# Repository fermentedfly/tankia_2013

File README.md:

# TANKIA 2013
There Are [still] No Kangaroos In Austria

This repository contains hard & software for TANKIA 2013 developed after end of season 2013

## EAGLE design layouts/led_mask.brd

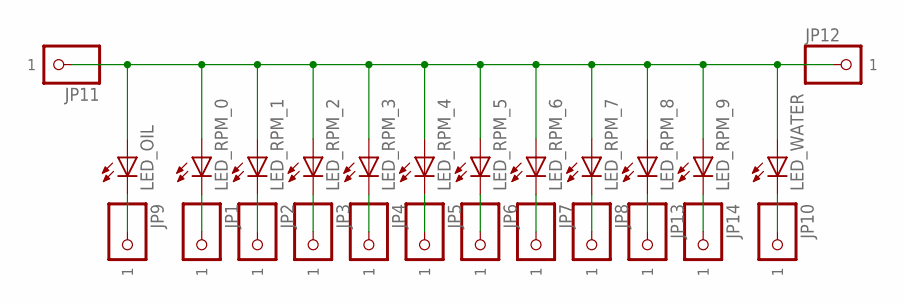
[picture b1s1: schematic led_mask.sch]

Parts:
JP1, JP2, JP3, JP4, JP5, JP6, JP7, JP8, JP9, JP10, JP11, JP12, JP13, JP14: PINHD-1X11.5X2.5MM_SMD; 1XSMD1.5X2.5MM
LED_OIL: LED3MM
LED_RPM_0, LED_RPM_1, LED_RPM_2, LED_RPM_3, LED_RPM_4, LED_RPM_5, LED_RPM_6, LED_RPM_7, LED_RPM_8, LED_RPM_9: LED3MM
LED_WATER: LED3MM

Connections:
unnamed: JP11.P$1, JP12.P$1, LED_OIL.A, LED_RPM_0.A, LED_RPM_1.A, LED_RPM_2.A, LED_RPM_3.A, LED_RPM_4.A, LED_RPM_5.A, LED_RPM_6.A, LED_RPM_7.A, LED_RPM_8.A, LED_RPM_9.A, LED_WATER.A
unnamed: JP3.P$1, LED_RPM_2.K (C)
unnamed: JP1.P$1, LED_RPM_0.K (C)
unnamed: JP2.P$1, LED_RPM_1.K (C)
unnamed: JP4.P$1, LED_RPM_3.K (C)
unnamed: JP5.P$1, LED_RPM_4.K (C)
unnamed: JP6.P$1, LED_RPM_5.K (C)
unnamed: JP7.P$1, LED_RPM_6.K (C)
unnamed: JP8.P$1, LED_RPM_7.K (C)
unnamed: JP9.P$1, LED_OIL.K (C)
unnamed: JP10.P$1, LED_WATER.K (C)
unnamed: JP13.P$1, LED_RPM_8.K (C)
unnamed: JP14.P$1, LED_RPM_9.K (C)

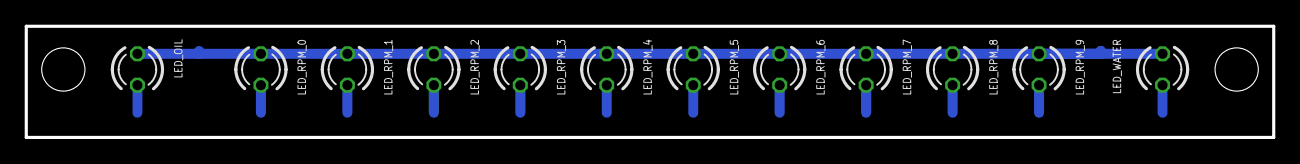
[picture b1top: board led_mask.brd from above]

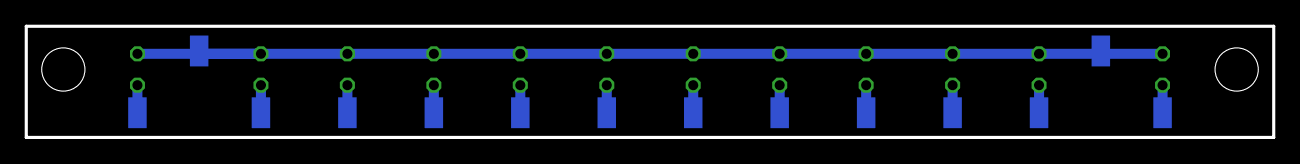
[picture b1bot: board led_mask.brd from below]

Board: 2 copper layers, 101.0 x 9.0 mm, 26 parts (14 on the bottom side), 13 nets.

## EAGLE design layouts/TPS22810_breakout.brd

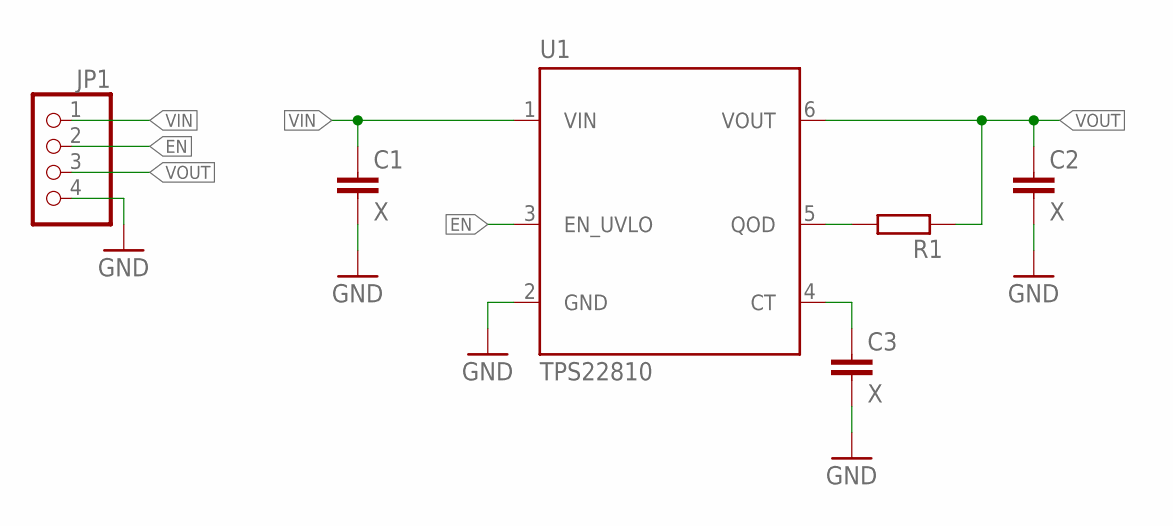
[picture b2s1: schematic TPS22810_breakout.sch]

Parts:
C1, C2, C3: X; C0603
JP1: PINHD-1X4; 1X04
R1: R-EU_R0603; R0603
U1: TPS22810; DBV-R-PDSO-G6

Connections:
EN: JP1.2, U1.3 (EN_UVLO)
GND: C1.2, C2.2, C3.2, JP1.4, U1.2 (GND)
unnamed: R1.2, U1.5 (QOD)
unnamed: C3.1, U1.4 (CT)
VIN: C1.1, JP1.1, U1.1 (VIN)
VOUT: C2.1, JP1.3, R1.1, U1.6 (VOUT)

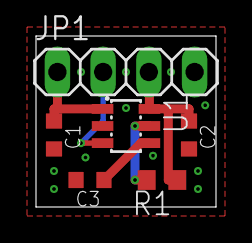
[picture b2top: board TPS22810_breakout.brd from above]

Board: 2 copper layers, 10.0 x 9.5 mm, 6 parts (0 on the bottom side), 6 nets.

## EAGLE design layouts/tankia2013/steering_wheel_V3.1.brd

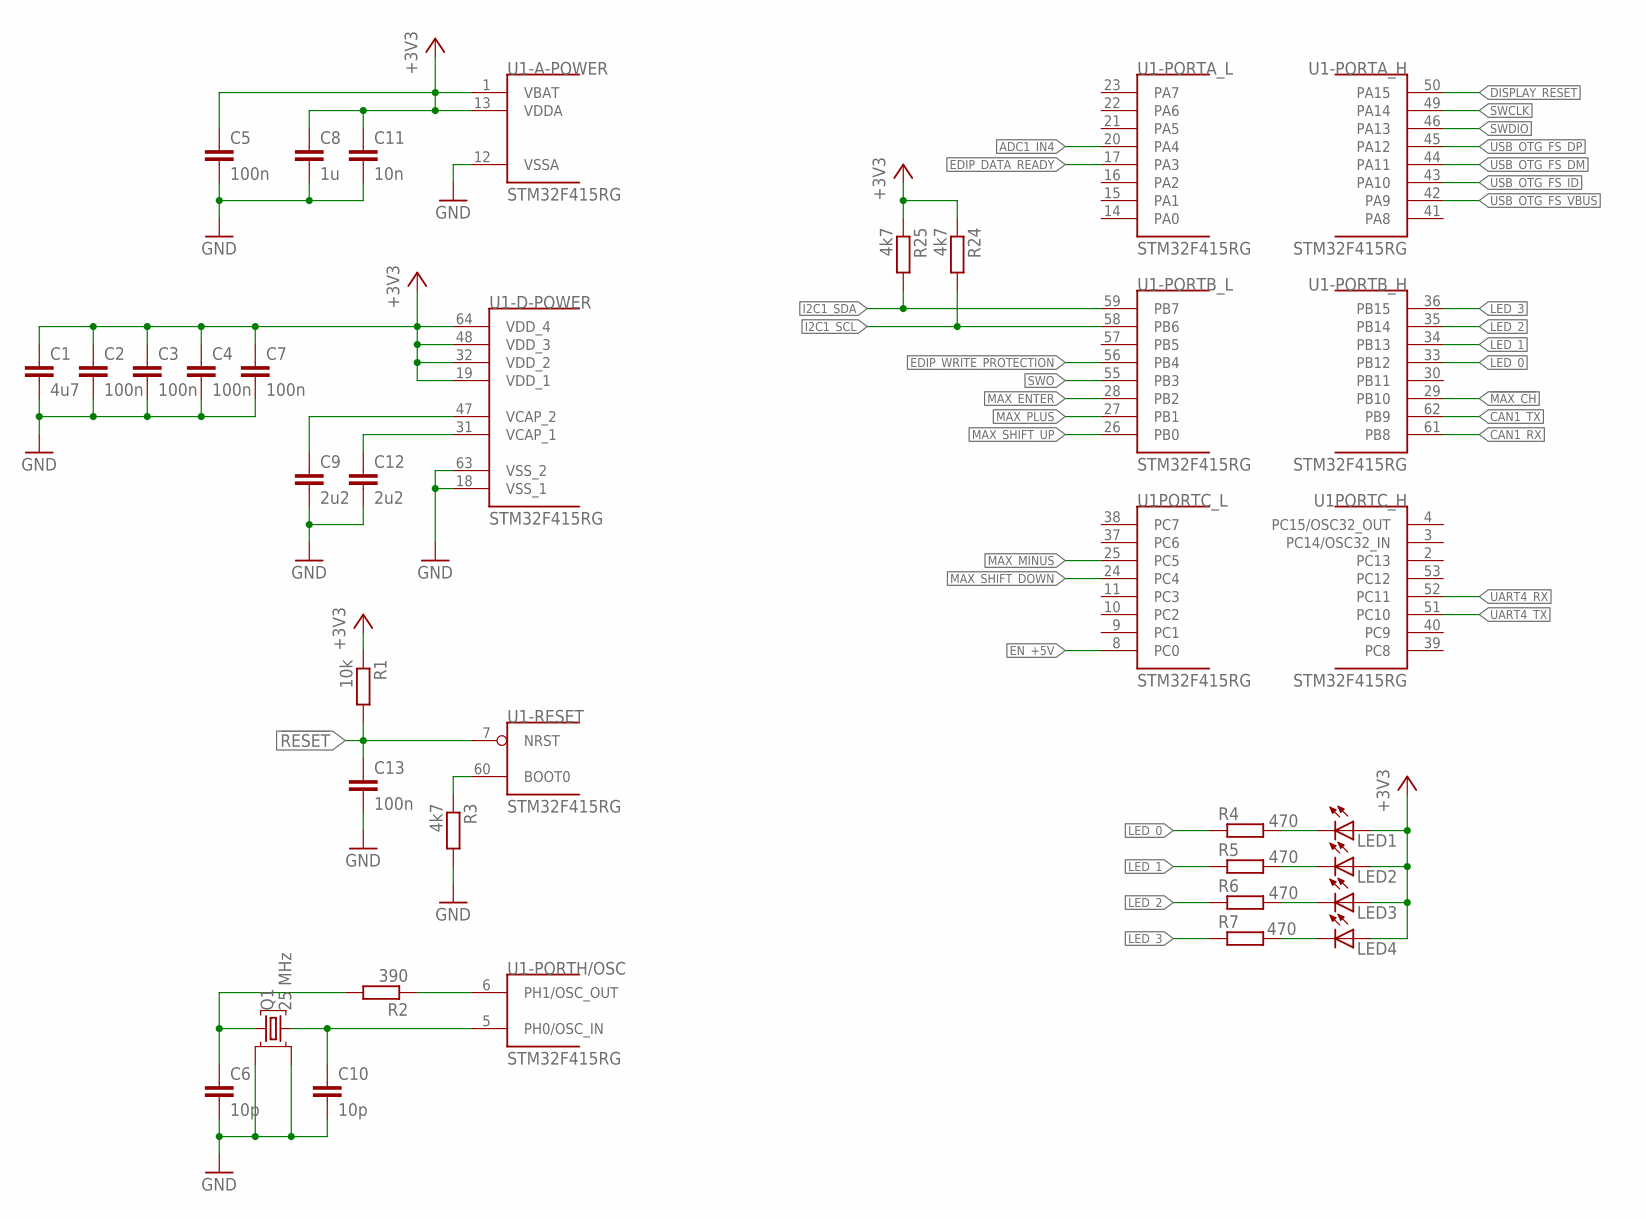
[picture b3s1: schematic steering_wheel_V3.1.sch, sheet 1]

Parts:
C1: 4u7; C0603
C2, C3, C4, C5, C7, C13: 100n; C0603
C6, C10: 10p; C0603
C8: 1u; C0603
C9, C12: 2u2; C0603
C11: 10n; C0603
LED1, LED2, LED3, LED4: LEDCHIPLED_0603; CHIPLED_0603
Q1: 25 MHz; 3.2X2.5MM-SMD
R1: 10k; R0603
R2: 390; R0603
R3, R24, R25: 4k7; R0603
R4, R5, R6, R7: 470; R0603
U1: STM32F415RG; LQFP64

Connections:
!MAX_CH: U1.29 (PB10); also elsewhere on the board
!RESET: C13.1, R1.2, U1.7 (NRST); also elsewhere on the board
+3V3: C1.1, C2.1, C3.1, C4.1, C5.1, C7.1, C8.1, C11.1, LED1.A, LED2.A, LED3.A, LED4.A, R1.1, R24.1, R25.1, U1.1 (VBAT), U1.13 (VDDA), U1.19 (VDD_1), U1.32 (VDD_2), U1.48 (VDD_3), U1.64 (VDD_4); also elsewhere on the board
ADC1_IN4: U1.20 (PA4); also elsewhere on the board
CAN1_RX: U1.61 (PB8); also elsewhere on the board
CAN1_TX: U1.62 (PB9); also elsewhere on the board
DISPLAY_RESET: U1.50 (PA15); also elsewhere on the board
EDIP_DATA_READY: U1.17 (PA3); also elsewhere on the board
EDIP_WRITE_PROTECTION: U1.56 (PB4); also elsewhere on the board
EN_+5V: U1.8 (PC0); also elsewhere on the board
GND: C1.2, C2.2, C3.2, C4.2, C5.2, C6.2, C7.2, C8.2, C9.2, C10.2, C11.2, C12.2, C13.2, Q1.2 (GND1), Q1.4 (GND2), R3.2, U1.12 (VSSA), U1.18 (VSS_1), U1.63 (VSS_2); also elsewhere on the board
I2C1_SCL: R24.2, U1.58 (PB6); also elsewhere on the board
I2C1_SDA: R25.2, U1.59 (PB7); also elsewhere on the board
LED_0: R4.1, U1.33 (PB12)
LED_1: R5.1, U1.34 (PB13)
LED_2: R6.1, U1.35 (PB14)
LED_3: R7.1, U1.36 (PB15)
MAX_ENTER: U1.28 (PB2); also elsewhere on the board
MAX_MINUS: U1.25 (PC5); also elsewhere on the board
MAX_PLUS: U1.27 (PB1); also elsewhere on the board
MAX_SHIFT_DOWN: U1.24 (PC4); also elsewhere on the board
MAX_SHIFT_UP: U1.26 (PB0); also elsewhere on the board
unnamed: C9.1, U1.47 (VCAP_2)
unnamed: C12.1, U1.31 (VCAP_1)
unnamed: R2.1, U1.6 (PH1/OSC_OUT)
unnamed: C10.1, Q1.3 (Q2), U1.5 (PH0/OSC_IN)
unnamed: LED4.C, R7.2
unnamed: R3.1, U1.60 (BOOT0)
unnamed: LED2.C, R5.2
unnamed: LED3.C, R6.2
unnamed: C6.1, Q1.1 (Q1), R2.2
unnamed: LED1.C, R4.2
SWCLK: U1.49 (PA14); also elsewhere on the board
SWDIO: U1.46 (PA13); also elsewhere on the board
SWO: U1.55 (PB3); also elsewhere on the board
UART4_RX: U1.52 (PC11); also elsewhere on the board
UART4_TX: U1.51 (PC10); also elsewhere on the board
USB_OTG_FS_DM: U1.44 (PA11); also elsewhere on the board
USB_OTG_FS_DP: U1.45 (PA12); also elsewhere on the board
USB_OTG_FS_ID: U1.43 (PA10); also elsewhere on the board
USB_OTG_FS_VBUS: U1.42 (PA9); also elsewhere on the board

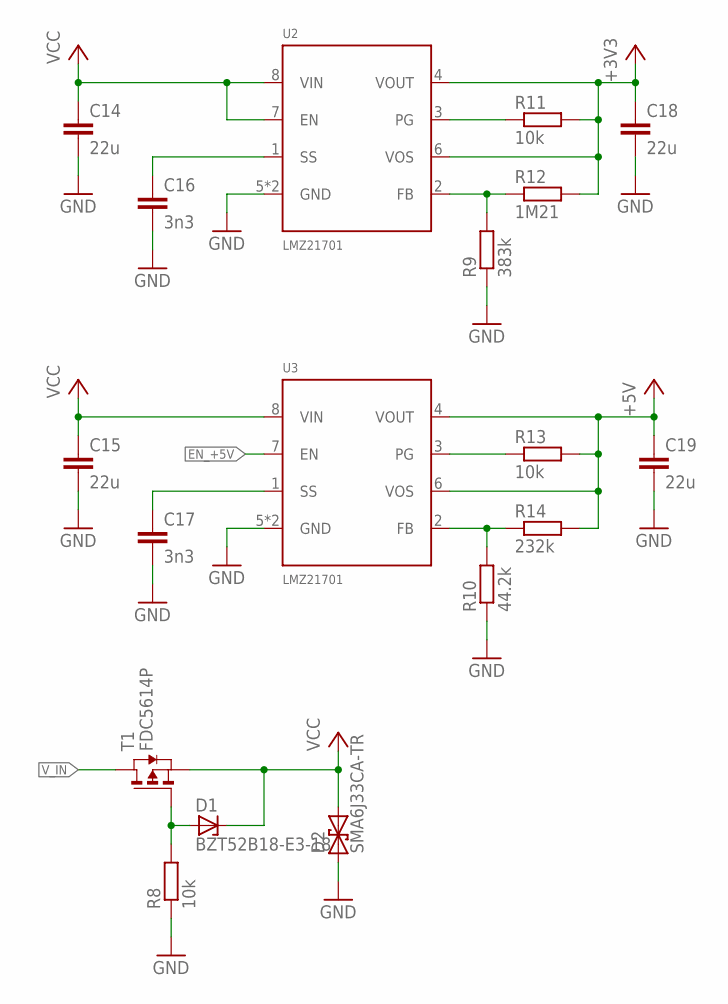
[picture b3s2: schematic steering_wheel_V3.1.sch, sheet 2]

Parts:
C14, C15, C18, C19: 22u; C1210
C16, C17: 3n3; C0603
D1: BZT52B18-E3-18; SOD123F
D2: SMA6J33CA-TR; DO214AC
R8, R11, R13: 10k; R0603
R9: 383k; R0603
R10: 44.2k; R0603
R12: 1M21; R0603
R14: 232k; R0603
T1: FDC5614P; SSOT6
U2, U3: LMZ21701; SIL0008E

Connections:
+3V3: C18.1, R11.2, R12.2, U2.4 (VOUT), U2.6 (VOS); also elsewhere on the board
+5V: C19.1, R13.2, R14.2, U3.4 (VOUT), U3.6 (VOS); also elsewhere on the board
EN_+5V: U3.7 (EN); also elsewhere on the board
GND: C14.2, C15.2, C16.2, C17.2, C18.2, C19.2, D2.A (1), R8.1, R9.1, R10.1, U2.5 (GND), U2.PAD (GND), U3.5 (GND), U3.PAD (GND); also elsewhere on the board
unnamed: D1.A, R8.2, T1.3 (G)
unnamed: C16.1, U2.1 (SS)
unnamed: C17.1, U3.1 (SS)
unnamed: R13.1, U3.3 (PG)
unnamed: R11.1, U2.3 (PG)
unnamed: R9.2, R12.1, U2.2 (FB)
unnamed: R10.2, R14.1, U3.2 (FB)
VCC: C14.1, C15.1, D1.C, D2.C (2), T1.4 (S), U2.7 (EN), U2.8 (VIN), U3.8 (VIN)
V_IN: T1.1 (D), T1.2 (D), T1.5 (D), T1.6 (D); also elsewhere on the board

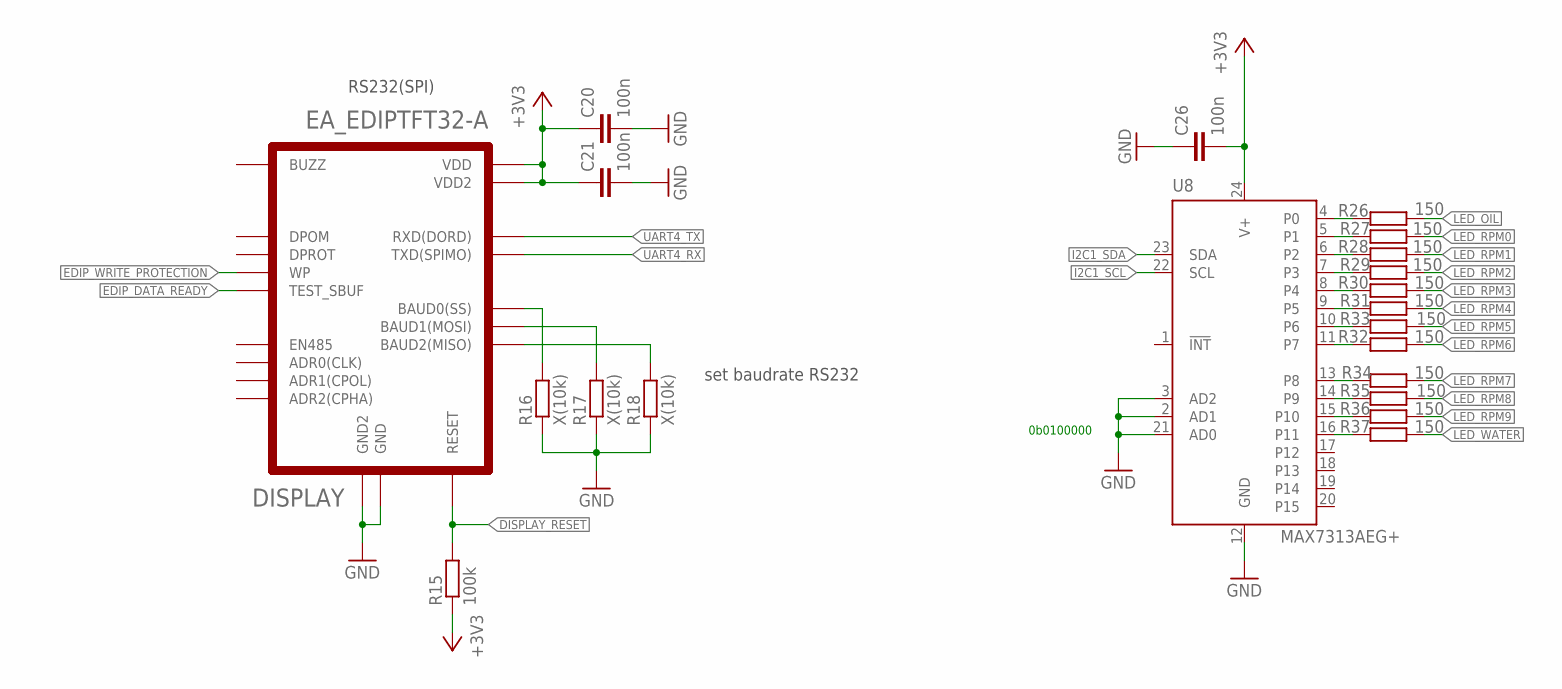
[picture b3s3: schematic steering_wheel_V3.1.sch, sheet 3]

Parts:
C20, C21, C26: 100n; C0603
DISPLAY: EA_EDIPTFT32-A; EDIPTFT32-A
R15: 100k; R0603
R16, R17, R18: X(10k); R0603
R26, R27, R28, R29, R30, R31, R32, R33, R34, R35, R36, R37: 150; R0603
U8: MAX7313AEG+; QSOP-24

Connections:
+3V3: C20.1, C21.1, C26.2, DISPLAY.P$2 (VDD), DISPLAY.P$22 (VDD2), R15.1, U8.24 (V+); also elsewhere on the board
DISPLAY_RESET: DISPLAY.P$5 (RESET), R15.2; also elsewhere on the board
EDIP_DATA_READY: DISPLAY.P$20 (TEST_SBUF); also elsewhere on the board
EDIP_WRITE_PROTECTION: DISPLAY.P$19 (WP); also elsewhere on the board
GND: C20.2, C21.2, C26.1, DISPLAY.P$1 (GND), DISPLAY.P$21 (GND2), R16.1, R17.1, R18.1, U8.2 (AD1), U8.3 (AD2), U8.12 (GND), U8.21 (AD0); also elsewhere on the board
I2C1_SCL: U8.22 (SCL); also elsewhere on the board
I2C1_SDA: U8.23 (SDA); also elsewhere on the board
LED_OIL: R26.1; also elsewhere on the board
LED_RPM0: R27.1; also elsewhere on the board
LED_RPM1: R28.1; also elsewhere on the board
LED_RPM2: R29.1; also elsewhere on the board
LED_RPM3: R30.1; also elsewhere on the board
LED_RPM4: R31.1; also elsewhere on the board
LED_RPM5: R33.1; also elsewhere on the board
LED_RPM6: R32.1; also elsewhere on the board
LED_RPM7: R34.1; also elsewhere on the board
LED_RPM8: R35.1; also elsewhere on the board
LED_RPM9: R36.1; also elsewhere on the board
LED_WATER: R37.1; also elsewhere on the board
unnamed: R26.2, U8.4 (P0)
unnamed: DISPLAY.P$8 (BAUD2(MISO)), R18.2
unnamed: R27.2, U8.5 (P1)
unnamed: DISPLAY.P$7 (BAUD1(MOSI)), R17.2
unnamed: DISPLAY.P$6 (BAUD0(SS)), R16.2
unnamed: R28.2, U8.6 (P2)
unnamed: R29.2, U8.7 (P3)
unnamed: R30.2, U8.8 (P4)
unnamed: R31.2, U8.9 (P5)
unnamed: R32.2, U8.11 (P7)
unnamed: R33.2, U8.10 (P6)
unnamed: R34.2, U8.13 (P8)
unnamed: R35.2, U8.14 (P9)
unnamed: R36.2, U8.15 (P10)
unnamed: R37.2, U8.16 (P11)
UART4_RX: DISPLAY.P$11 (TXD(SPIMO)); also elsewhere on the board
UART4_TX: DISPLAY.P$10 (RXD(DORD)); also elsewhere on the board

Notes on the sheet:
set baudrate RS232
0b0100000

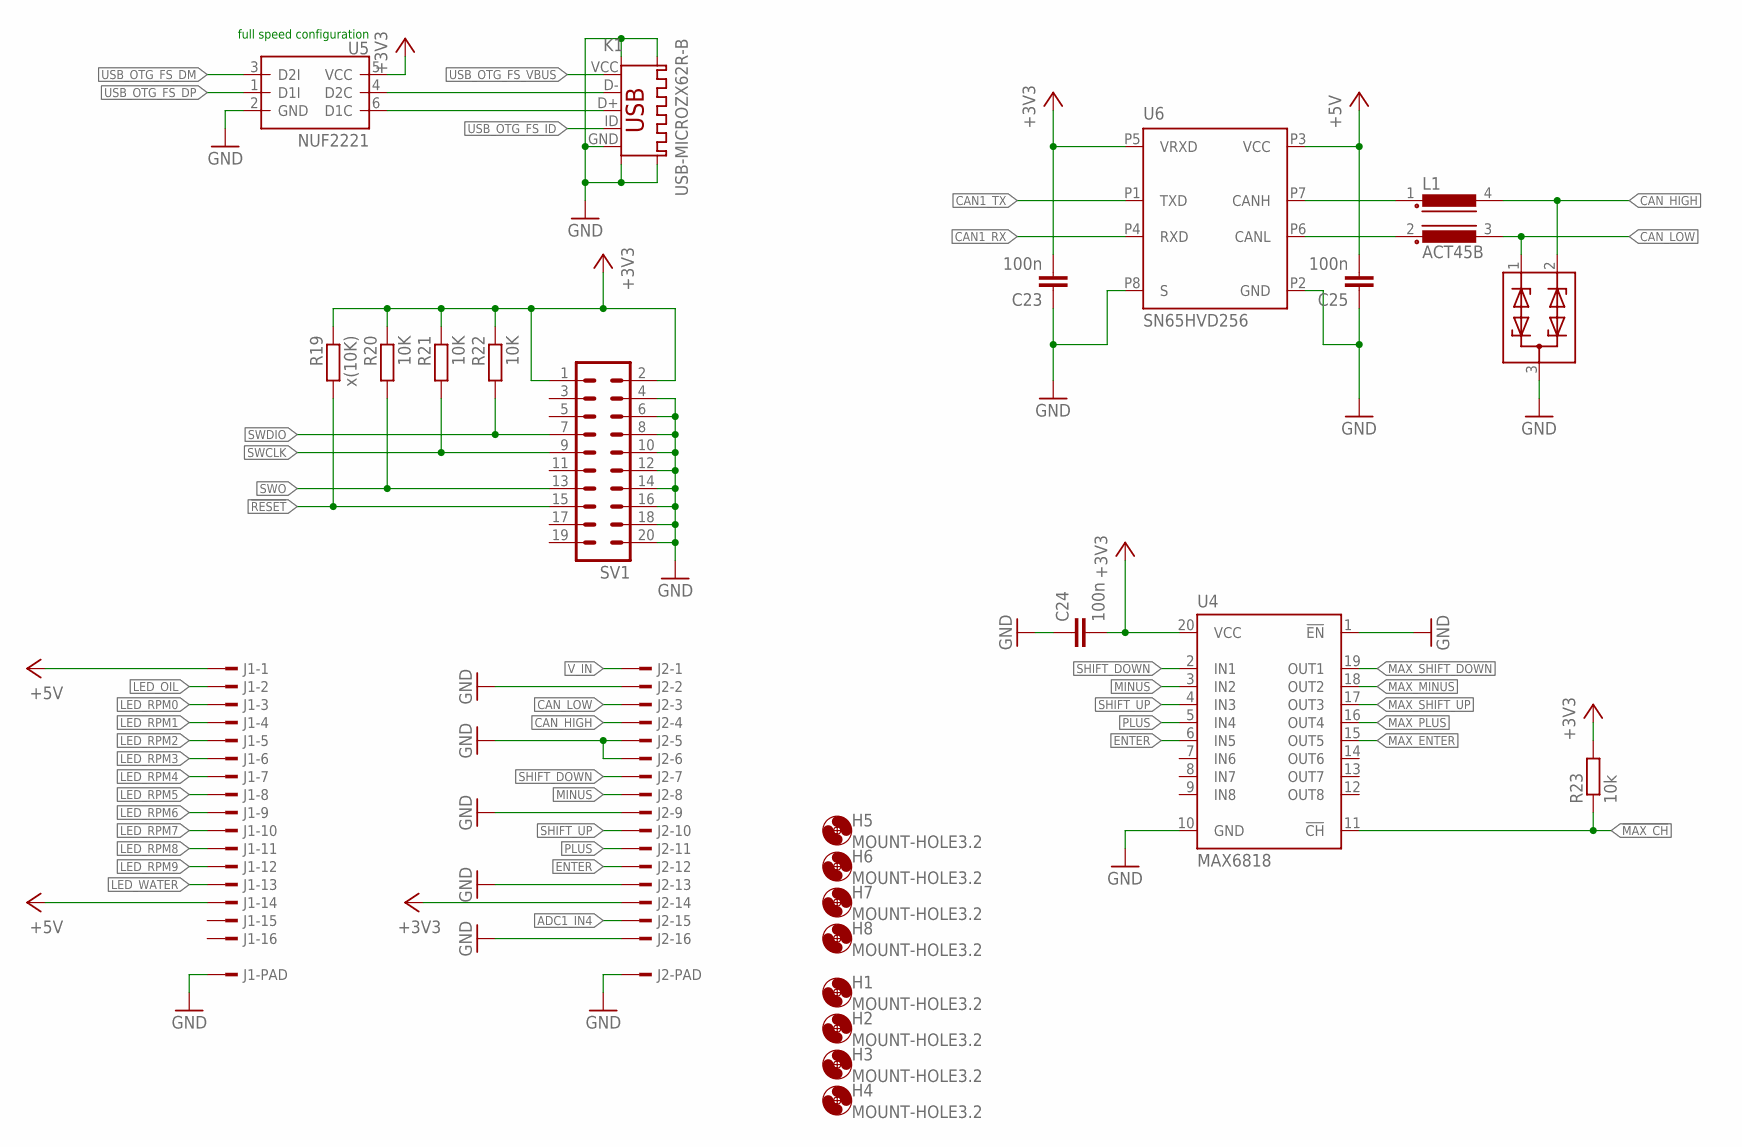
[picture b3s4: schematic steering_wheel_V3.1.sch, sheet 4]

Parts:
C23, C24, C25: 100n; C0603
D3: PESD1CAN-U; SOT-323
H1, H2, H3, H4, H5, H6, H7, H8: MOUNT-HOLE3.2; 3,2
J1, J2: 1-292227-6
K1: USB-MICROZX62R-B; ZX62R-B
L1: ACT45B
R19: x(10K); R0603
R20, R21, R22: 10K; R0603
R23: 10k; R0603
SV1: ML20
U4: MAX6818; SSOP-20
U5: NUF2221; SOT363
U6: SN65HVD256; SOIC8

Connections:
!MAX_CH: R23.1, U4.11 (!CH); also elsewhere on the board
+3V3: C23.2, C24.2, J2.14, R19.1, R20.1, R21.1, R22.1, R23.2, SV1.1, SV1.2, U4.20 (VCC), U5.5 (VCC), U6.P5 (VRXD); also elsewhere on the board
+5V: C25.2, J1.1, J1.14, U6.P3 (VCC); also elsewhere on the board
ADC1_IN4: J2.15; also elsewhere on the board
CAN1_RX: U6.P4 (RXD); also elsewhere on the board
CAN1_TX: U6.P1 (TXD); also elsewhere on the board
CAN_HIGH: D3.2, J2.4, L1.4
CAN_LOW: D3.1, J2.3, L1.3
ENTER: J2.12, U4.6 (IN5)
GND: C23.1, C24.1, C25.1, D3.3, J1.PAD1, J1.PAD2, J2.2, J2.5, J2.6, J2.9, J2.13, J2.16, J2.PAD1, J2.PAD2, K1.GND, K1.P$6 (GND3), K1.P$7 (GND4), K1.P$8 (GND1), K1.P$9 (GND2), SV1.4, SV1.6, SV1.8, SV1.10, SV1.12, SV1.14, SV1.16, SV1.18, SV1.20, U4.1 (!EN), U4.10 (GND), U5.2 (GND), U6.P2 (GND), U6.P8 (S); also elsewhere on the board
LED_OIL: J1.2; also elsewhere on the board
LED_RPM0: J1.3; also elsewhere on the board
LED_RPM1: J1.4; also elsewhere on the board
LED_RPM2: J1.5; also elsewhere on the board
LED_RPM3: J1.6; also elsewhere on the board
LED_RPM4: J1.7; also elsewhere on the board
LED_RPM5: J1.8; also elsewhere on the board
LED_RPM6: J1.9; also elsewhere on the board
LED_RPM7: J1.10; also elsewhere on the board
LED_RPM8: J1.11; also elsewhere on the board
LED_RPM9: J1.12; also elsewhere on the board
LED_WATER: J1.13; also elsewhere on the board
MAX_ENTER: U4.15 (OUT5); also elsewhere on the board
MAX_MINUS: U4.18 (OUT2); also elsewhere on the board
MAX_PLUS: U4.16 (OUT4); also elsewhere on the board
MAX_SHIFT_DOWN: U4.19 (OUT1); also elsewhere on the board
MAX_SHIFT_UP: U4.17 (OUT3); also elsewhere on the board
MINUS: J2.8, U4.3 (IN2)
unnamed: L1.1, U6.P7 (CANH)
unnamed: L1.2, U6.P6 (CANL)
unnamed: R19.2, SV1.15
PLUS: J2.11, U4.5 (IN4)
SHIFT_DOWN: J2.7, U4.2 (IN1)
SHIFT_UP: J2.10, U4.4 (IN3)
SWCLK: R21.2, SV1.9; also elsewhere on the board
SWDIO: R22.2, SV1.7; also elsewhere on the board
SWO: R20.2, SV1.13; also elsewhere on the board
USB_DM: K1.D-, U5.4 (D2C)
USB_DP: K1.D+, U5.6 (D1C)
USB_OTG_FS_DM: U5.3 (D2I); also elsewhere on the board
USB_OTG_FS_DP: U5.1 (D1I); also elsewhere on the board
USB_OTG_FS_ID: K1.ID; also elsewhere on the board
USB_OTG_FS_VBUS: K1.VCC; also elsewhere on the board
V_IN: J2.1; also elsewhere on the board

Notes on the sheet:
full speed configuration

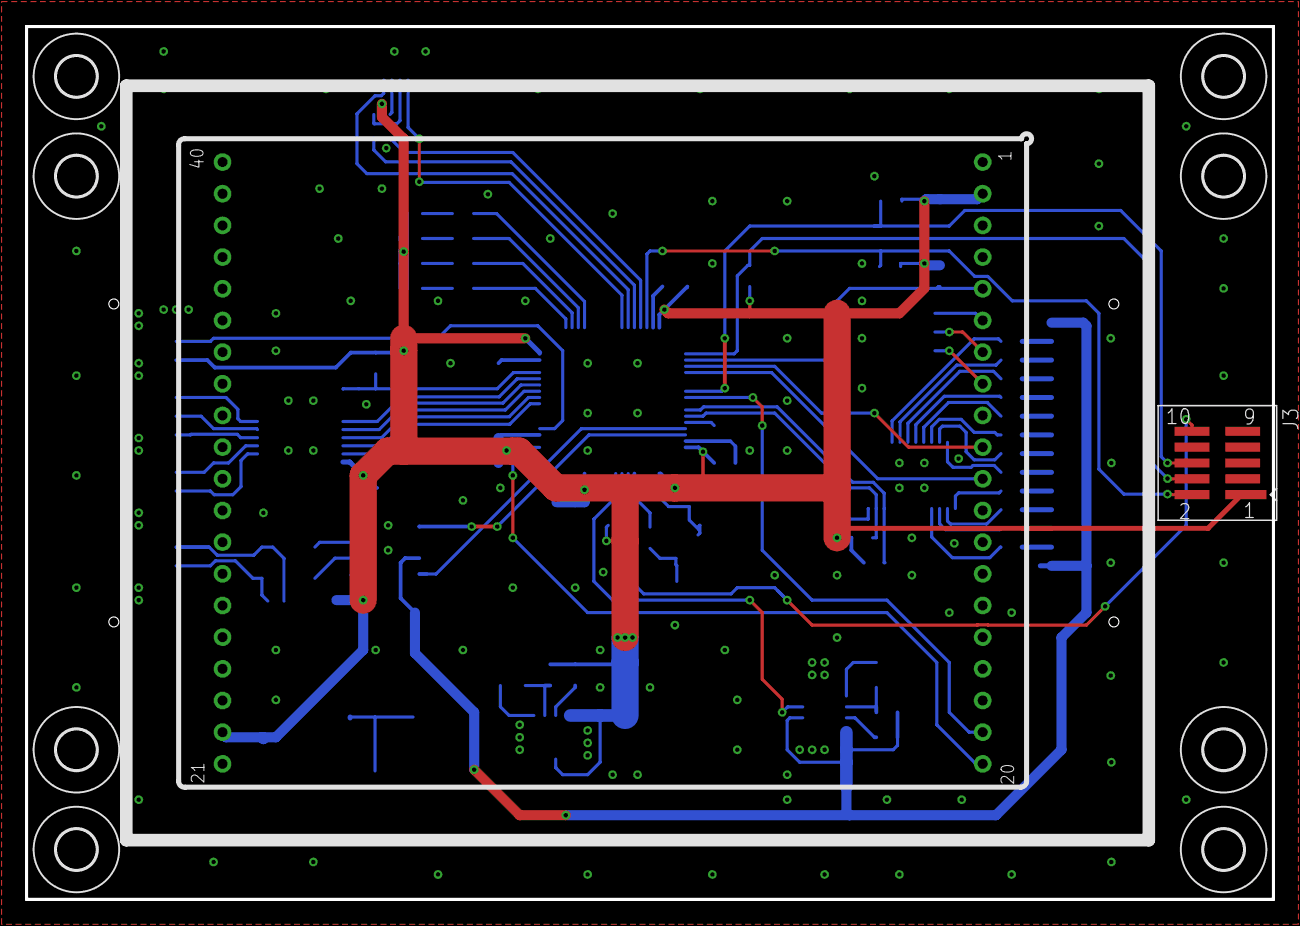
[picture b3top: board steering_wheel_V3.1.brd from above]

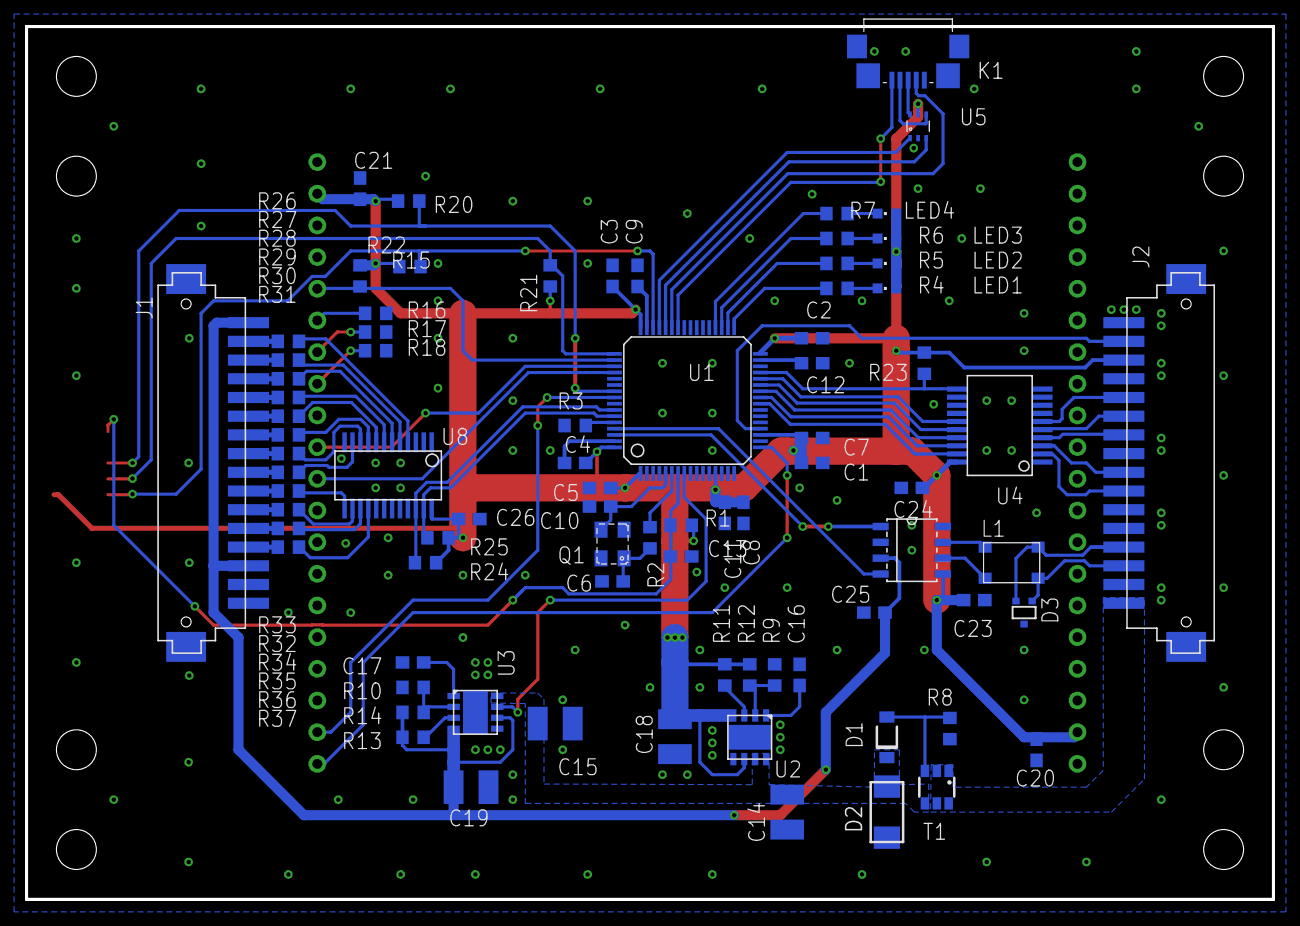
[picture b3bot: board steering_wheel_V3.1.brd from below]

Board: 2 copper layers, 100.0 x 70.0 mm, 91 parts (81 on the bottom side), 89 nets.

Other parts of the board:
J3: FTSH-105-01-F-DV-K; FTSH-105-01-XXX-DV-K

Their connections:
!RESET: J3.10; also elsewhere on the board
+3V3: J3.1; also elsewhere on the board
GND: J3.3, J3.5; also elsewhere on the board
SWCLK: J3.4; also elsewhere on the board
SWDIO: J3.2; also elsewhere on the board
SWO: J3.6; also elsewhere on the board

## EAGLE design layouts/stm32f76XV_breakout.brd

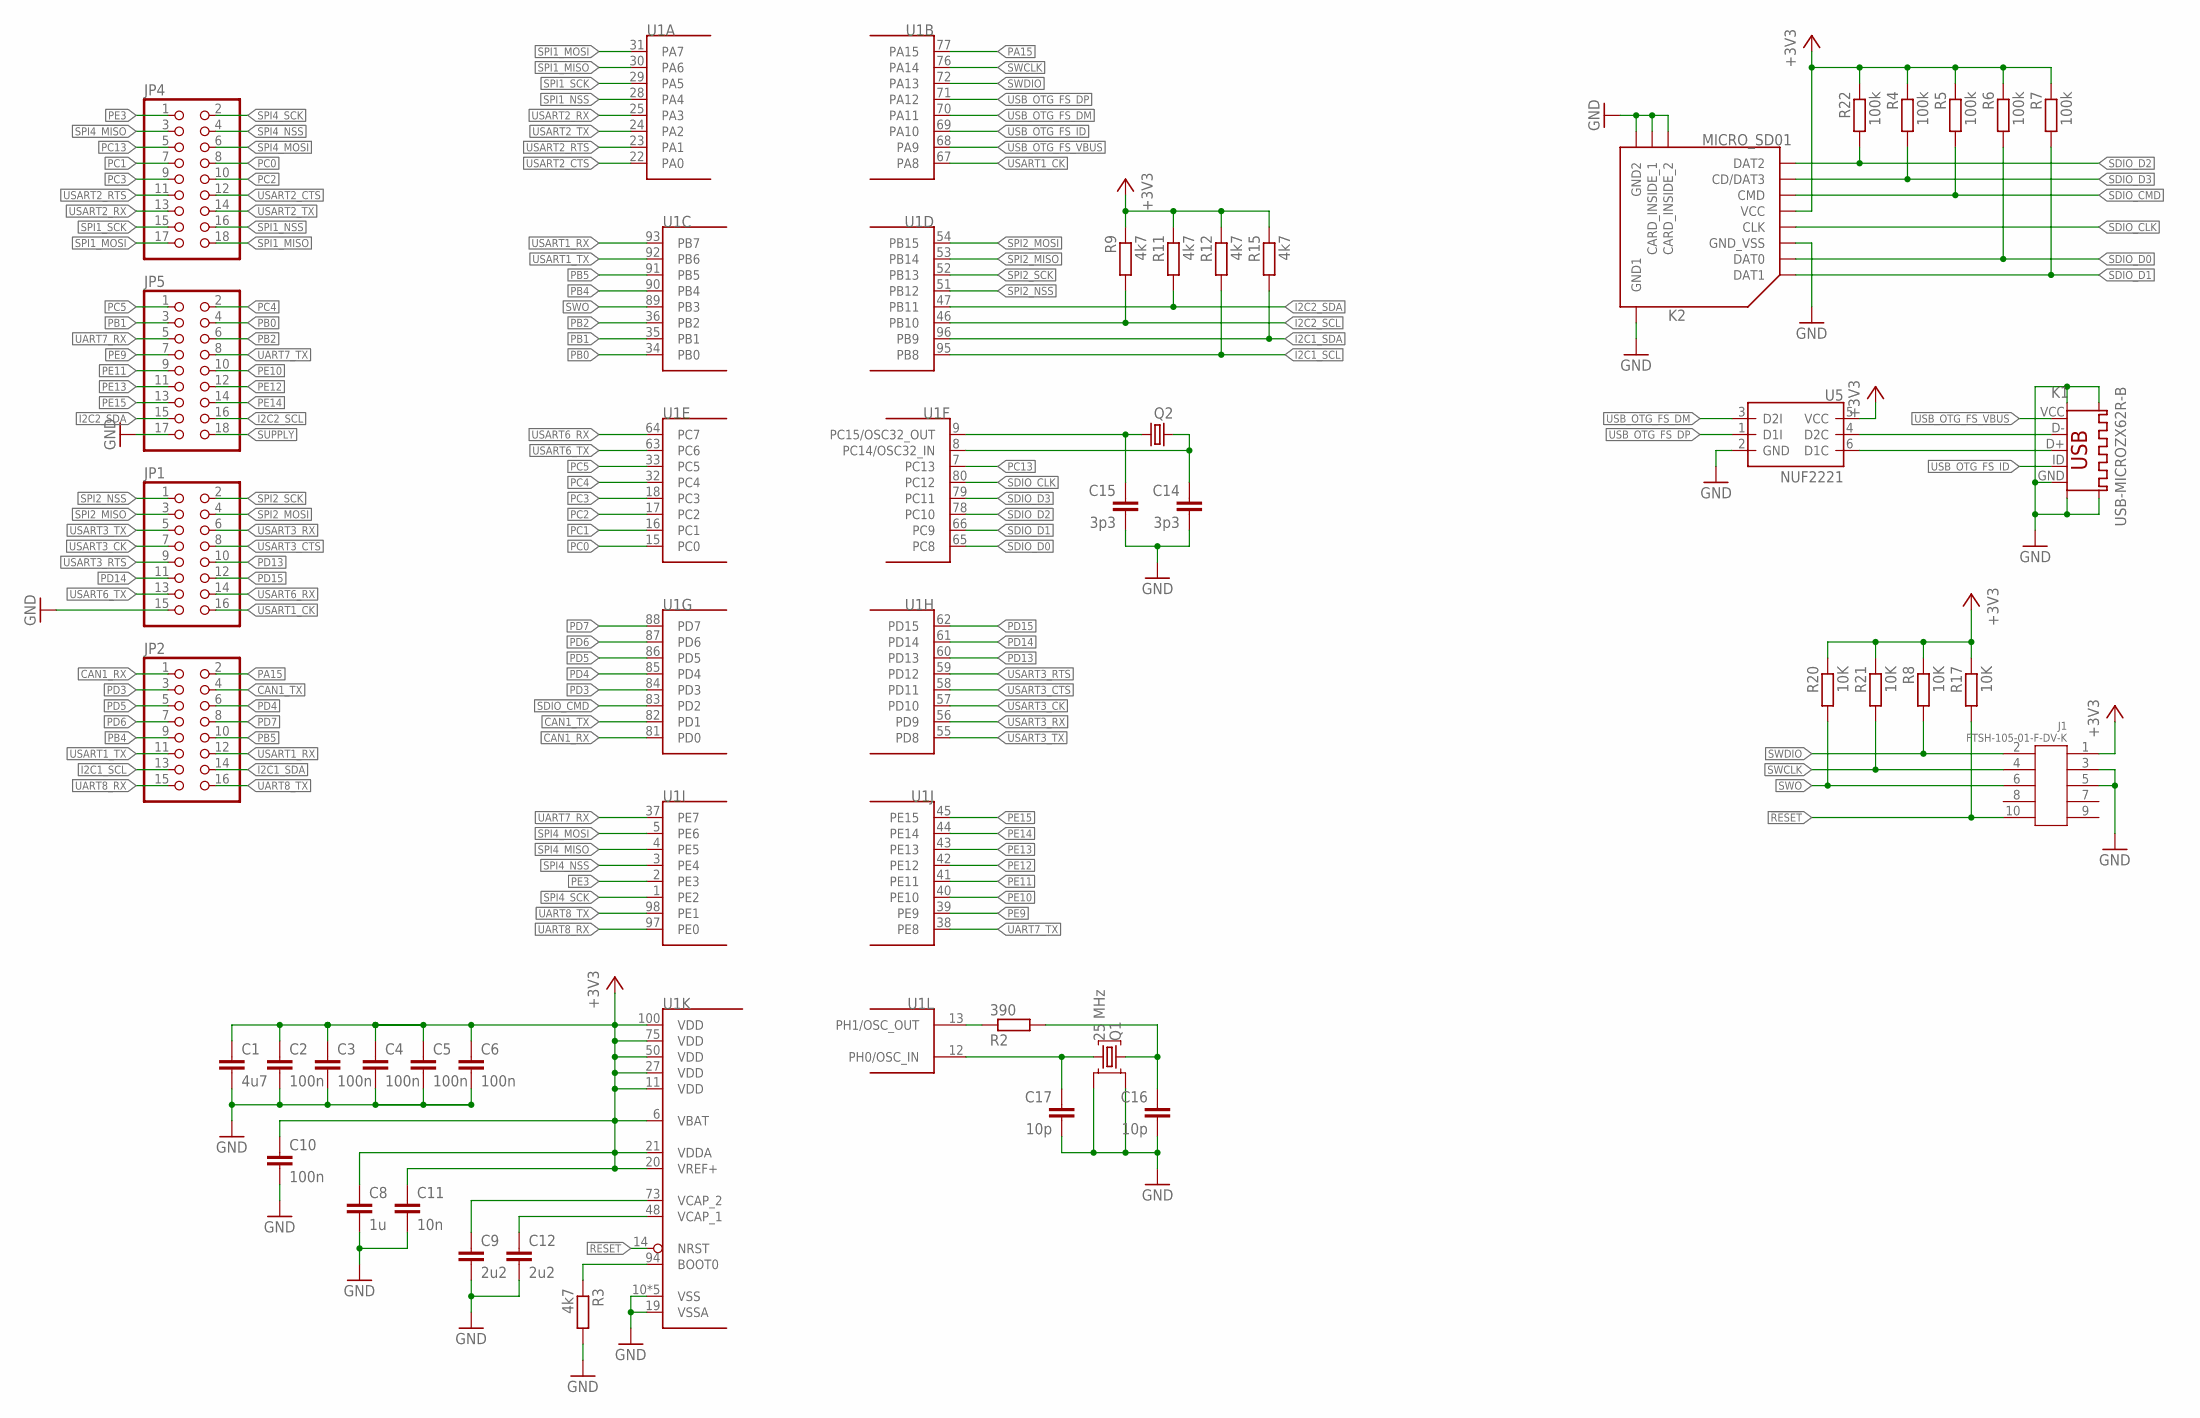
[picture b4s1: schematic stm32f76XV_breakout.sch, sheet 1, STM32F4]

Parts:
C1: 4u7; C0603
C2, C3, C4, C5, C6, C10: 100n; C0603
C8: 1u; C0603
C9, C12: 2u2; C0603
C11: 10n; C0603
C14, C15: 3p3; C0603
C16, C17: 10p; C0603
J1: FTSH-105-01-F-DV-K; FTSH-105-01-XXX-DV-K
JP1, JP2: PINHD-2X8; 2X08
JP4, JP5: PINHD-2X9; 2X09
K1: USB-MICROZX62R-B; ZX62R-B
K2: MICRO_SD01; MICRO_SD_473093751
Q1: 25 MHz; 3.2X2.5MM-SMD
Q2: CRYSTAL_ECX-34S; 3.2X1.5MM-SMD
R2: 390; R0603
R3, R9, R11, R12, R15: 4k7; R0603
R4, R5, R6, R7, R22: 100k; R0603
R8, R17, R20, R21: 10K; R0603
U1: STM32F76XVXT; LQFP-100_14X14MM
U5: NUF2221; SOT363

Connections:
!RESET: J1.10, R17.2, U1.14 (NRST)
+3V3: C1.1, C2.1, C3.1, C4.1, C5.1, C6.1, C8.1, C10.1, C11.1, J1.1, K2.VCC, R4.1, R5.1, R6.1, R7.1, R8.1, R9.1, R11.1, R12.1, R15.1, R17.1, R20.1, R21.1, R22.1, U1.6 (VBAT), U1.11 (VDD), U1.20 (VREF+), U1.21 (VDDA), U1.27 (VDD), U1.50 (VDD), U1.75 (VDD), U1.100 (VDD), U5.5 (VCC); also elsewhere on the board
CAN1_RX: JP2.1, U1.81 (PD0)
CAN1_TX: JP2.4, U1.82 (PD1)
GND: C1.2, C2.2, C3.2, C4.2, C5.2, C6.2, C8.2, C9.2, C10.2, C11.2, C12.2, C14.2, C15.2, C16.2, C17.2, J1.3, J1.5, JP1.15, JP5.17, K1.GND, K1.P$6 (GND3), K1.P$7 (GND4), K1.P$8 (GND1), K1.P$9 (GND2), K2.C_SW1 (CARD_INSIDE_1), K2.C_SW2 (CARD_INSIDE_2), K2.GND1, K2.GND2, K2.GND_VSS, Q1.2 (GND1), Q1.4 (GND2), R3.2, U1.10 (VSS), U1.19 (VSSA), U1.26 (VSS), U1.49 (VSS), U1.74 (VSS), U1.99 (VSS), U5.2 (GND); also elsewhere on the board
I2C1_SCL: JP2.13, R12.2, U1.95 (PB8)
I2C1_SDA: JP2.14, R15.2, U1.96 (PB9)
I2C2_SCL: JP5.16, R9.2, U1.46 (PB10)
I2C2_SDA: JP5.15, R11.2, U1.47 (PB11)
unnamed: C9.1, U1.73 (VCAP_2)
unnamed: C12.1, U1.48 (VCAP_1)
unnamed: R2.1, U1.13 (PH1/OSC_OUT)
unnamed: C17.1, Q1.3 (Q2), U1.12 (PH0/OSC_IN)
unnamed: R3.1, U1.94 (BOOT0)
unnamed: C15.1, Q2.Q2 (2), U1.9 (PC15/OSC32_OUT)
unnamed: C14.1, Q2.Q1 (1), U1.8 (PC14/OSC32_IN)
unnamed: C16.1, Q1.1 (Q1), R2.2
PA15: JP2.2, U1.77 (PA15)
PB0: JP5.4, U1.34 (PB0)
PB1: JP5.3, U1.35 (PB1)
PB2: JP5.6, U1.36 (PB2)
PB4: JP2.9, U1.90 (PB4)
PB5: JP2.10, U1.91 (PB5)
PC0: JP4.8, U1.15 (PC0)
PC1: JP4.7, U1.16 (PC1)
PC2: JP4.10, U1.17 (PC2)
PC3: JP4.9, U1.18 (PC3)
PC4: JP5.2, U1.32 (PC4)
PC5: JP5.1, U1.33 (PC5)
PC13: JP4.5, U1.7 (PC13)
PD3: JP2.3, U1.84 (PD3)
PD4: JP2.6, U1.85 (PD4)
PD5: JP2.5, U1.86 (PD5)
PD6: JP2.7, U1.87 (PD6)
PD7: JP2.8, U1.88 (PD7)
PD13: JP1.10, U1.60 (PD13)
PD14: JP1.11, U1.61 (PD14)
PD15: JP1.12, U1.62 (PD15)
PE3: JP4.1, U1.2 (PE3)
PE9: JP5.7, U1.39 (PE9)
PE10: JP5.10, U1.40 (PE10)
PE11: JP5.9, U1.41 (PE11)
PE12: JP5.12, U1.42 (PE12)
PE13: JP5.11, U1.43 (PE13)
PE14: JP5.14, U1.44 (PE14)
PE15: JP5.13, U1.45 (PE15)
SDIO_CLK: K2.CLK, U1.80 (PC12)
SDIO_CMD: K2.CMD, R5.2, U1.83 (PD2)
SDIO_D0: K2.DAT0, R6.2, U1.65 (PC8)
SDIO_D1: K2.DAT1, R7.2, U1.66 (PC9)
SDIO_D2: K2.DAT2, R22.2, U1.78 (PC10)
SDIO_D3: K2.CD/DAT3, R4.2, U1.79 (PC11)
SPI1_MISO: JP4.18, U1.30 (PA6)
SPI1_MOSI: JP4.17, U1.31 (PA7)
SPI1_NSS: JP4.16, U1.28 (PA4)
SPI1_SCK: JP4.15, U1.29 (PA5)
SPI2_MISO: JP1.3, U1.53 (PB14)
SPI2_MOSI: JP1.4, U1.54 (PB15)
SPI2_NSS: JP1.1, U1.51 (PB12)
SPI2_SCK: JP1.2, U1.52 (PB13)
SPI4_MISO: JP4.3, U1.4 (PE5)
SPI4_MOSI: JP4.6, U1.5 (PE6)
SPI4_NSS: JP4.4, U1.3 (PE4)
SPI4_SCK: JP4.2, U1.1 (PE2)
SUPPLY: JP5.18; also elsewhere on the board
SWCLK: J1.4, R21.2, U1.76 (PA14)
SWDIO: J1.2, R8.2, U1.72 (PA13)
SWO: J1.6, R20.2, U1.89 (PB3)
UART7_RX: JP5.5, U1.37 (PE7)
UART7_TX: JP5.8, U1.38 (PE8)
UART8_RX: JP2.15, U1.97 (PE0)
UART8_TX: JP2.16, U1.98 (PE1)
USART1_CK: JP1.16, U1.67 (PA8)
USART1_RX: JP2.12, U1.93 (PB7)
USART1_TX: JP2.11, U1.92 (PB6)
USART2_CTS: JP4.12, U1.22 (PA0)
USART2_RTS: JP4.11, U1.23 (PA1)
USART2_RX: JP4.13, U1.25 (PA3)
USART2_TX: JP4.14, U1.24 (PA2)
USART3_CK: JP1.7, U1.57 (PD10)
USART3_CTS: JP1.8, U1.58 (PD11)
USART3_RTS: JP1.9, U1.59 (PD12)
USART3_RX: JP1.6, U1.56 (PD9)
USART3_TX: JP1.5, U1.55 (PD8)
USART6_RX: JP1.14, U1.64 (PC7)
USART6_TX: JP1.13, U1.63 (PC6)
USB_DM: K1.D-, U5.4 (D2C)
USB_DP: K1.D+, U5.6 (D1C)
USB_OTG_FS_DM: U1.70 (PA11), U5.3 (D2I)
USB_OTG_FS_DP: U1.71 (PA12), U5.1 (D1I)
USB_OTG_FS_ID: K1.ID, U1.69 (PA10)
USB_OTG_FS_VBUS: K1.VCC, U1.68 (PA9)

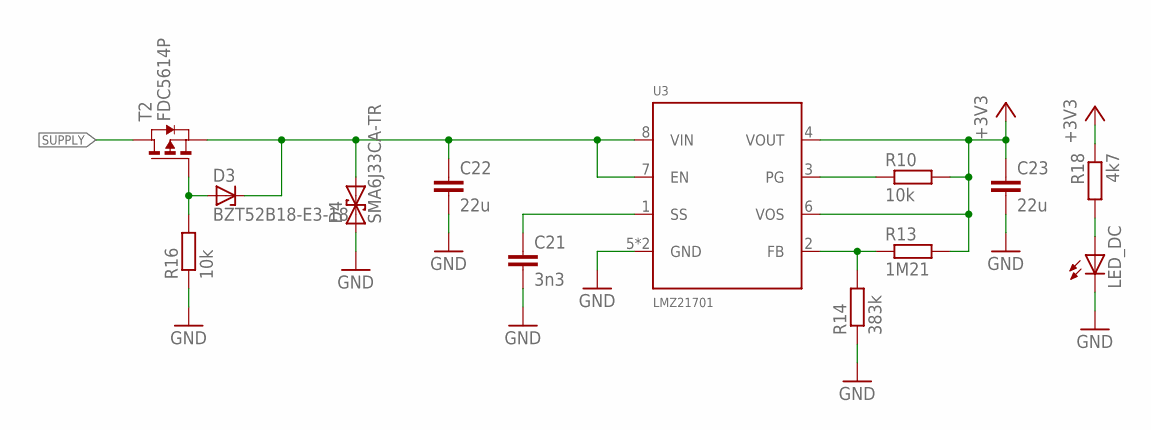
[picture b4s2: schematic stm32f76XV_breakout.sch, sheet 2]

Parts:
C21: 3n3; C0603
C22, C23: 22u; C1210
D3: BZT52B18-E3-18; SOD123F
D4: SMA6J33CA-TR; DO214AC
LED_DC: LEDCHIPLED_0603; CHIPLED_0603
R10, R16: 10k; R0603
R13: 1M21; R0603
R14: 383k; R0603
R18: 4k7; R0603
T2: FDC5614P; SSOT6
U3: LMZ21701; SIL0008E

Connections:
+3V3: C23.1, R10.2, R13.2, R18.1, U3.4 (VOUT), U3.6 (VOS); also elsewhere on the board
GND: C21.2, C22.2, C23.2, D4.A (1), LED_DC.C, R14.1, R16.1, U3.5 (GND), U3.PAD (GND); also elsewhere on the board
LMZ_FB: R13.1, R14.2, U3.2 (FB)
LMZ_PG: R10.1, U3.3 (PG)
LMZ_SS: C21.1, U3.1 (SS)
LMZ_VIN: C22.1, D3.C, D4.C (2), T2.4 (S), U3.7 (EN), U3.8 (VIN)
unnamed: LED_DC.A, R18.2
unnamed: D3.A, R16.2, T2.3 (G)
SUPPLY: T2.1 (D), T2.2 (D), T2.5 (D), T2.6 (D); also elsewhere on the board
